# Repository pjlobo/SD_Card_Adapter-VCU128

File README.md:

# SD_Card_Adapter-VCU128

KiCad project of a daughter card for Xilinx UltraScale+ VCU128 FPGA Evaluationn Kit adding a SD card socket and a JTAG header

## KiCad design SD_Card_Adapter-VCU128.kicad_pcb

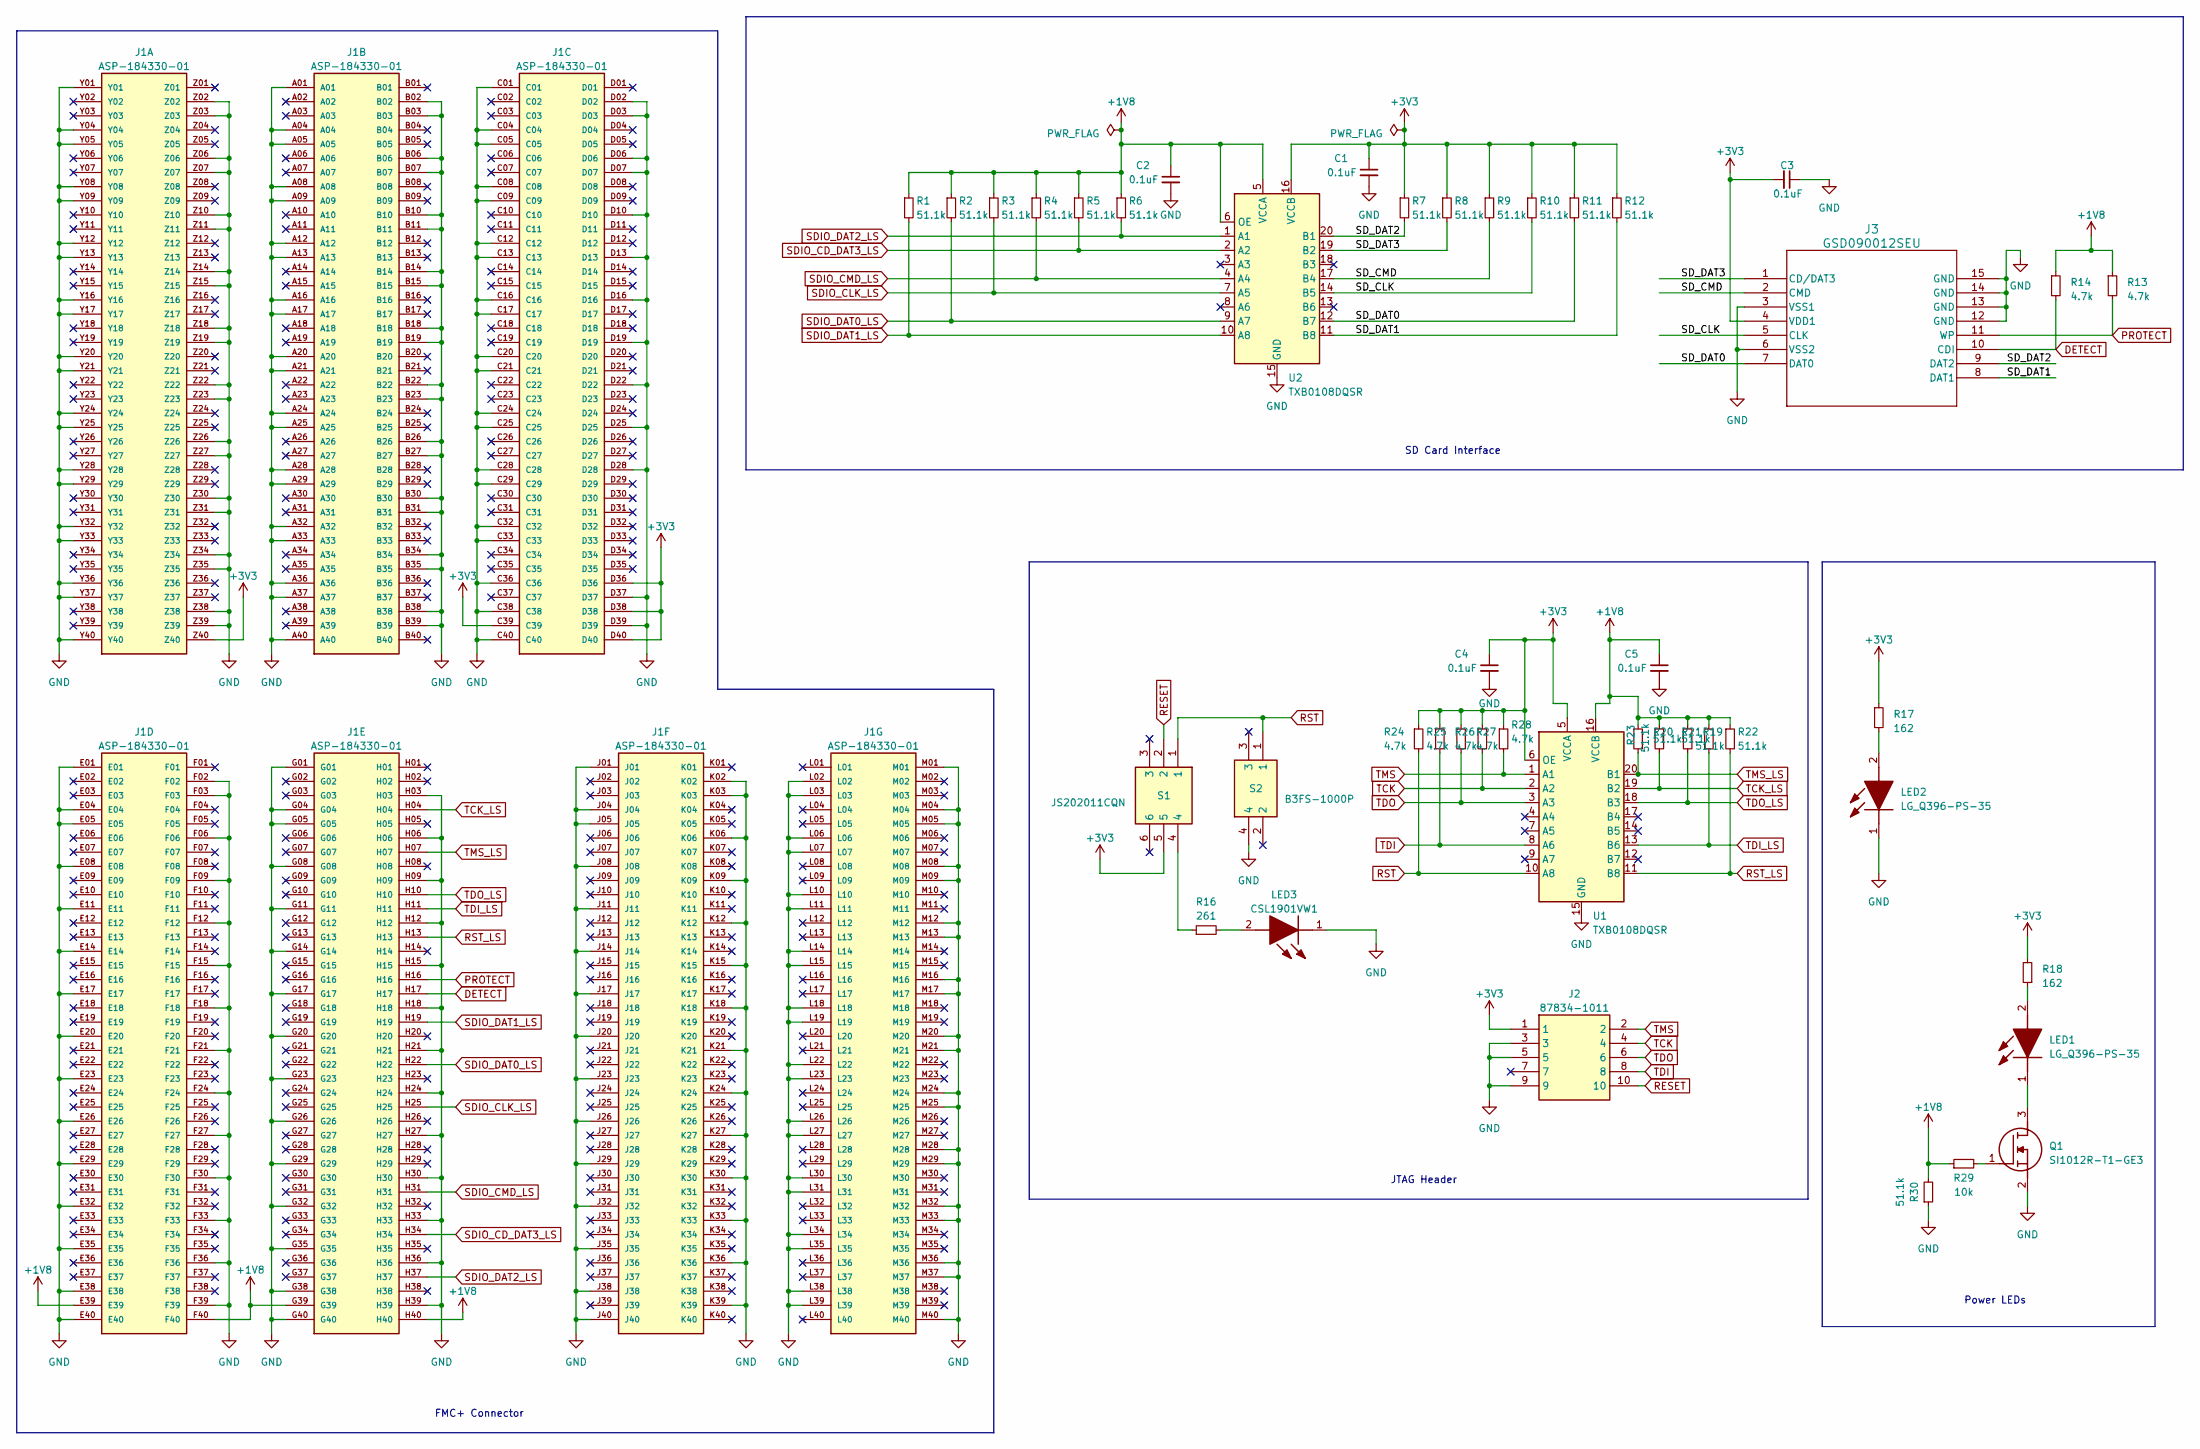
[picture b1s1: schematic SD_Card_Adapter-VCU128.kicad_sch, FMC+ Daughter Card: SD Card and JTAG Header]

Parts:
C1, C2, C3, C4, C5: 0.1uF; C_0603_1608Metric_Pad1.08x0.95mm_HandSolder
J1: ASP-184330-01; SAMTEC_ASP-184330-01; PARTREV C
J2: 87834-1011; 878341011; Mouser Part Number 538-87834-1011
J3: GSD090012SEU; GSD090012SEU_AMP
LED1, LED2: LG_Q396-PS-35; LEDC1608X40N; Manufacturer_Part_Number LG Q396-PS-35-0-20-R18
LED3: CSL1901VW1; LEDC1608X65N; Mouser Part Number 755-CSL1901VW1
Q1: SI1012R-T1-GE3; SOT50P160X80-3N; Mouser Part Number 781-SI1012R-T1-GE3
R1, R2, R3, R4, R5, R6, R7, R8, R9, R10, R11, R12, R19, R20, R21, R22, R23, R30: 51.1k; R_0603_1608Metric_Pad0.98x0.95mm_HandSolder
R13, R14, R24, R25, R26, R27, R28: 4.7k; R_0603_1608Metric_Pad0.98x0.95mm_HandSolder
R16: 261; R_0603_1608Metric_Pad0.98x0.95mm_HandSolder
R17, R18: 162; R_0603_1608Metric_Pad0.98x0.95mm_HandSolder
R29: 10k; R_0603_1608Metric_Pad0.98x0.95mm_HandSolder
S1: JS202011CQN; Mouser Part Number 611-JS202011CQN
S2: B3FS-1000P; Mouser Part Number 653-B3FS-1000P
U1, U2: TXB0108DQSR; USON-20_2x4mm_P0.4mm

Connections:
+1V8: C2.1, C5.1, J1.E39, J1.F40, J1.G39, J1.H40, R1.1, R2.1, R3.1, R4.1, R5.1, R6.1, R13.1, R14.1, R19.1, R20.1, R21.1, R22.1, R23.1, R29.1, R30.2, U1.16 (VCCB), U2.5 (VCCA), U2.6 (OE)
+3V3: C1.1, C3.2, C4.1, J1.C39, J1.D36, J1.D38, J1.D40, J1.Z40, J2.1, J3.4 (VDD1), R7.1, R8.1, R9.1, R10.1, R11.1, R12.1, R17.1, R18.2, R24.1, R25.1, R26.1, R27.1, R28.1, S1.5, U1.5 (VCCA), U1.6 (OE), U2.16 (VCCB)
/SD_CLK: J3.5 (CLK), R10.2, U2.14 (B5)
/SD_CMD: J3.2 (CMD), R9.2, U2.17 (B4)
/SD_DAT0: J3.7 (DAT0), R11.2, U2.12 (B7)
/SD_DAT1: J3.8 (DAT1), R12.2, U2.11 (B8)
/SD_DAT2: J3.9 (DAT2), R7.2, U2.20 (B1)
/SD_DAT3: J3.1 (CD/DAT3), R8.2, U2.19 (B2)
DETECT: J1.H17, J3.10 (CDI), R14.2
GND: C1.2, C2.2, C3.1, C4.2, C5.2, J1.A01, J1.A04, J1.A05, J1.A08, J1.A09, J1.A12, J1.A13, J1.A16, J1.A17, J1.A20, J1.A21, J1.A24, J1.A25, J1.A28, J1.A29, J1.A32, J1.A33, J1.A36, J1.A37, J1.A40, J1.B02, J1.B03, J1.B06, J1.B07, J1.B10, J1.B11, J1.B14, J1.B15, J1.B18, J1.B19, J1.B22, J1.B23, J1.B26, J1.B27, J1.B30, J1.B31, J1.B34, J1.B35, J1.B38, J1.B39, J1.C01, J1.C04, J1.C05, J1.C08, J1.C09, J1.C12, J1.C13, J1.C16, J1.C17, J1.C20, J1.C21, J1.C24, J1.C25, J1.C28, J1.C29, J1.C32, J1.C33, J1.C36, J1.C38, J1.C40, J1.D02, J1.D03, J1.D06, J1.D07, J1.D10, J1.D13, J1.D16, J1.D19, J1.D22, J1.D25, J1.D28, J1.D37, J1.D39, J1.E01, J1.E04, J1.E05, J1.E08, J1.E11, J1.E14, J1.E17, J1.E20, J1.E23, J1.E26, J1.E29, J1.E32, J1.E35, J1.E38, J1.E40, J1.F02, J1.F03, J1.F06, J1.F09, J1.F12, J1.F15, J1.F18, J1.F21, J1.F24, J1.F27, J1.F30, J1.F33, J1.F36, J1.F39, J1.G01, J1.G04, J1.G05, J1.G08, J1.G11, J1.G14, J1.G17, J1.G20, J1.G23, J1.G26, J1.G29, J1.G32, J1.G35, J1.G38, J1.G40, J1.H03, J1.H06, J1.H09, J1.H12, J1.H15, J1.H18, J1.H21, J1.H24, J1.H27, J1.H30, J1.H33, J1.H36, J1.H39, J1.J01, J1.J04, J1.J05, J1.J08, J1.J11, J1.J14, J1.J17, J1.J20, J1.J23, J1.J26, J1.J29, J1.J32, J1.J35, J1.J38, J1.J40, J1.K02, J1.K03, J1.K06, J1.K09, J1.K12, J1.K15, J1.K18, J1.K21, J1.K24, J1.K27, J1.K30, J1.K33, J1.K36, J1.K39, J1.L02, J1.L03, J1.L06, J1.L07, J1.L10, J1.L11, J1.L14, J1.L15, J1.L18, J1.L19, J1.L22, J1.L23, J1.L26, J1.L27, J1.L30, J1.L31, J1.L34, J1.L35, J1.L38, J1.L39, J1.M01, J1.M04, J1.M05, J1.M08, J1.M09, J1.M12, J1.M13, J1.M16, J1.M17, J1.M20, J1.M21, J1.M24, J1.M25, J1.M28, J1.M29, J1.M32, J1.M33, J1.M36, J1.M37, J1.M40, J1.Y01, J1.Y04, J1.Y05, J1.Y08, J1.Y09, J1.Y12, J1.Y13, J1.Y16, J1.Y17, J1.Y20, J1.Y21, J1.Y24, J1.Y25, J1.Y28, J1.Y29, J1.Y32, J1.Y33, J1.Y36, J1.Y37, J1.Y40, J1.Z02, J1.Z03, J1.Z06, J1.Z07, J1.Z10, J1.Z11, J1.Z14, J1.Z15, J1.Z18, J1.Z19, J1.Z22, J1.Z23, J1.Z26, J1.Z27, J1.Z30, J1.Z31, J1.Z34, J1.Z35, J1.Z38, J1.Z39, J2.3, J2.5, J2.9, J3.3 (VSS1), J3.6 (VSS2), J3.12 (GND), J3.13 (GND), J3.14 (GND), J3.15 (GND), LED2.1 (K), LED3.1 (K), Q1.2 (S), R30.1, S2.4, U1.15 (GND), U2.15 (GND)
unnamed: LED1.2 (A), R18.1
unnamed: LED1.1 (K), Q1.3 (D)
unnamed: LED2.2 (A), R17.2
unnamed: LED3.2 (A), R16.2
unnamed: Q1.1 (G), R29.2
unnamed: R16.1, S1.4
PROTECT: J1.H16, J3.11 (WP), R13.2
RESET: J2.10, S1.2
RST: R24.2, S1.1, S2.1, U1.10 (A8)
RST_LS: J1.H13, R22.2, U1.11 (B8)
SDIO_CD_DAT3_LS: J1.H34, R5.2, U2.2 (A2)
SDIO_CLK_LS: J1.H25, R3.2, U2.7 (A5)
SDIO_CMD_LS: J1.H31, R4.2, U2.4 (A4)
SDIO_DAT0_LS: J1.H22, R2.2, U2.9 (A7)
SDIO_DAT1_LS: J1.H19, R1.2, U2.10 (A8)
SDIO_DAT2_LS: J1.H37, R6.2, U2.1 (A1)
TCK: J2.4, R27.2, U1.2 (A2)
TCK_LS: J1.H04, R20.2, U1.19 (B2)
TDI: J2.8, R25.2, U1.8 (A6)
TDI_LS: J1.H11, R19.2, U1.13 (B6)
TDO: J2.6, R26.2, U1.3 (A3)
TDO_LS: J1.H10, R21.2, U1.18 (B3)
TMS: J2.2, R28.2, U1.1 (A1)
TMS_LS: J1.H07, R23.2, U1.20 (B1)

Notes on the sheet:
JTAG Header
SD Card Interface
Power LEDs
FMC+ Connector

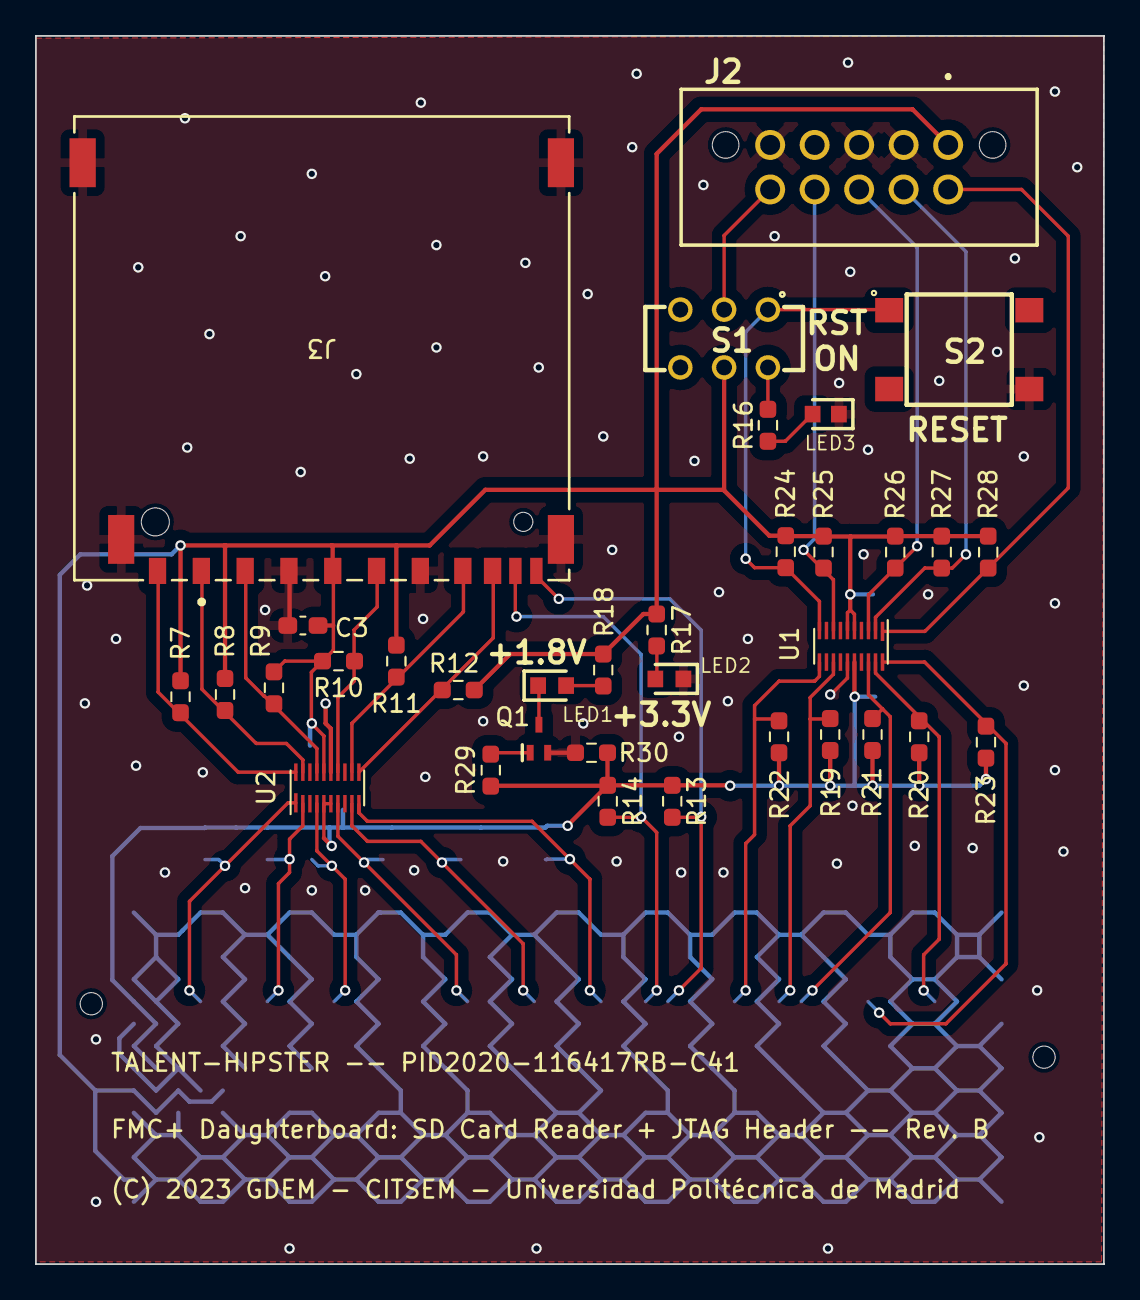
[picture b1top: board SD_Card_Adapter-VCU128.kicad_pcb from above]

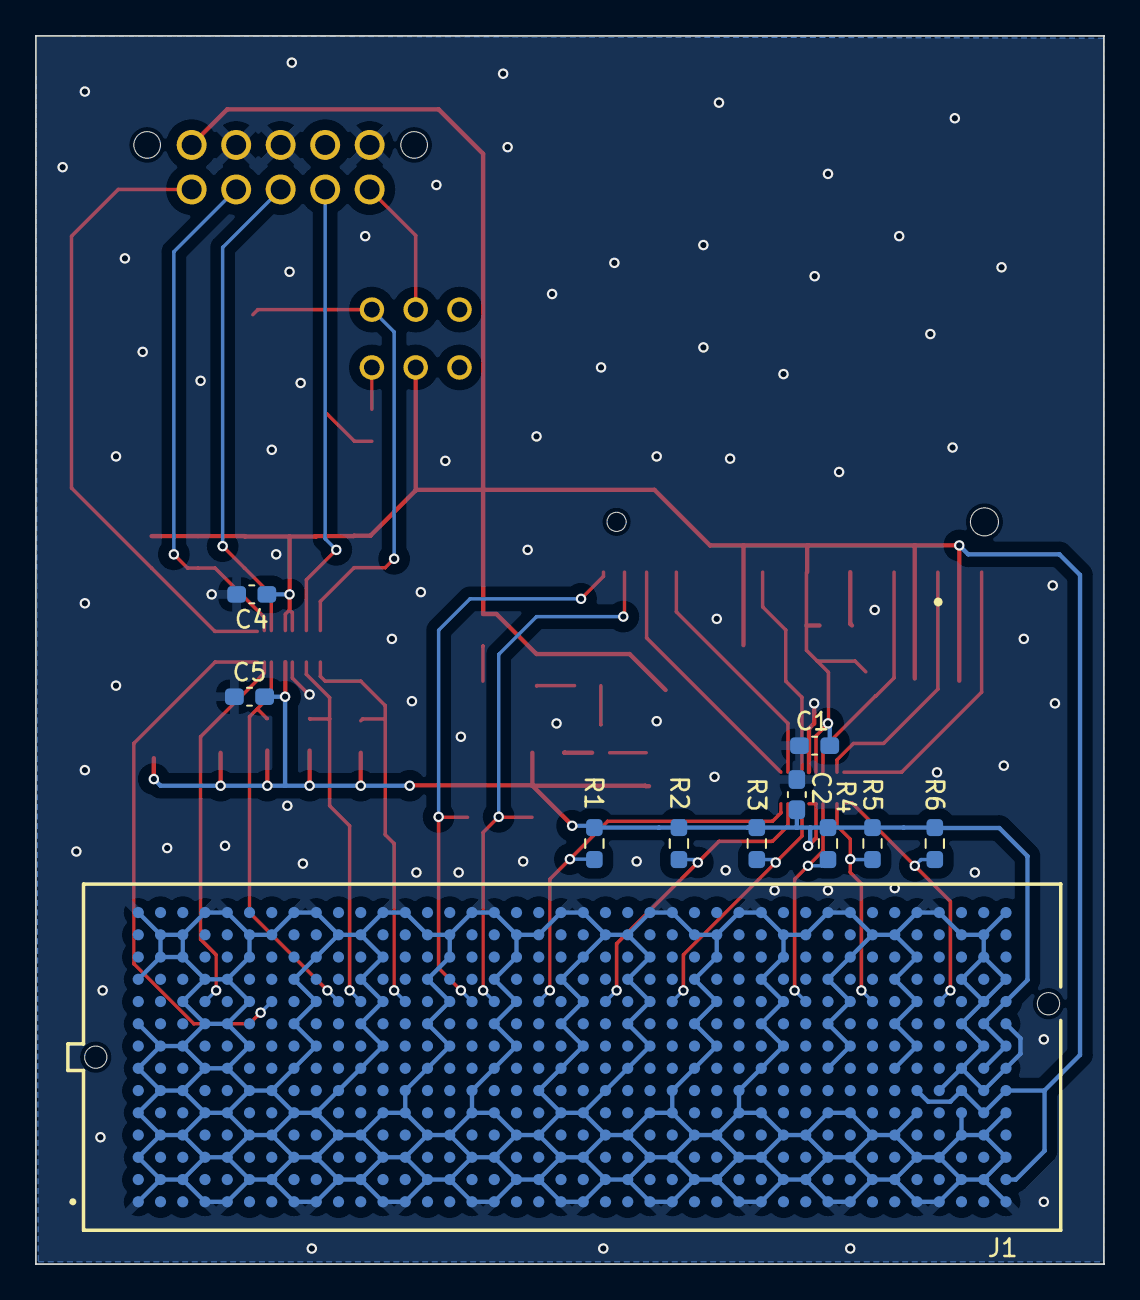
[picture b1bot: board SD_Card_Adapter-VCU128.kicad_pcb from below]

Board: 2 copper layers, 61.0 x 70.1 mm, 45 parts (11 on the bottom side), 34 nets.

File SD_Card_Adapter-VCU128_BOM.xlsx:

Manufacturer Part Number | Description | Reference Designator | Quantity | Manufacturer | Supplier Part Number | Supplier name
0603X7R104JT1AT | Multilayer Ceramic Capacitors MLCC- SMD/SMT 25V 0.1uF 0603 X7R 5% Tol | C1, C2, C3, C4, C5 | 5 | ATC / KYOCERA AVX | 581-0603X7R104JT1AT | Mouser
ASP-184330-01 | SEARAY FMC+ Connector, 560 contacts | J1 | 1 | Samtec Inc. | 200-ASP-184330-01 | Mouser
87834-1011 | HDR SHROUDED 10P | J2 | 1 | Molex | 538-87834-1011 | Mouser
GSD090012SEU | SD CARD CONNECTOR 9 POS, SMT | J3 | 1 | Amphenol Commercial Products | 523-GSD090012SEU | Mouser
LG Q396-PS-35-0-20-R18 | SMD LED GREEN | LED1, LED2 | 2 | ams OSRAM | 720-LGQ396A3964 | Mouser
CSL1901VW1 | SMD LED RED | LED3 | 1 | ROHM Semiconductor | 755-CSL1901VW1 | Mouser
SI1012R-T1-GE3 | MOSFET 20V 0.6A 175mW 700mohm @ 4.5V SC-75A-3 package | Q1 | 1 | Vishay Semiconductors | 781-SI1012R-T1-GE3 | Mouser
CR0603-FX-5112ELF | Thick Film Resistors - SMD 51.1K ohm 1% 0603 (1608 metric) | R1, R2, R3, R4, R5, R6, R7, R8, R9, R10, R11, R12, R19, R20, R21, R22, R23, R30 | 18 | Bourns | 652-CR0603FX-5112ELF | Mouser
CR0603-FX-4701ELF | Thick Film Resistors - SMD 4.7K ohm 1% 0603 (1608 metric) | R13, R14, R24, R25, R26, R27, R28 | 7 | Bourns | 652-CR0603FX-4701ELF | Mouser
CR0603-FX-2610ELF | Thick Film Resistors - SMD 261 ohm 1% 0603 (1608 metric) | R16 | 1 | Bourns | 652-CR0603FX-2610ELF | Mouser
CR0603-FX-1620ELF | Thick Film Resistors - SMD 162 ohm 1% 0603 (1608 metric) | R17, R18 | 2 | Bourns | 652-CR0603FX-1620ELF | Mouser
CR0603-FX-1002ELF | Thick Film Resistors - SMD 10K ohm 1% 0603 (1608 metric) | R29 | 1 | Bourns | 652-CR0603FX-1002ELF | Mouser
JS202011CQN | Slide Swidth DPDT THRU HOLE .3A | S1 | 1 | C&K | 611-JS202011CQN | Mouser
B3FS-1000P | SPST Tactile Switch SMD 6x6x3.1mm | S2 | 1 | Omron | 653-B3FS-1000P | Mouser
TXB0108DQSR | 8B Bidir Voltage-Level Translator | U2,U1 | 2 | Texas Instruments | 595-TXB0108DQSR | Mouser

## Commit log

2023-06-08 Update PCB date and version, migrate FMC+ connector's 3D model to git-lfs
2023-06-15 Revision B.
    All signals have been moved to row H of FMC+ connector J1
    because the ones in row M are connected to FPGA pins that
    are dedicated to high speed transceivers.

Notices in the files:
SD_Card_Adapter-VCU128.kicad_pcb:
(C) 2023 GDEM - CITSEM - Universidad Politécnica de Madrid
